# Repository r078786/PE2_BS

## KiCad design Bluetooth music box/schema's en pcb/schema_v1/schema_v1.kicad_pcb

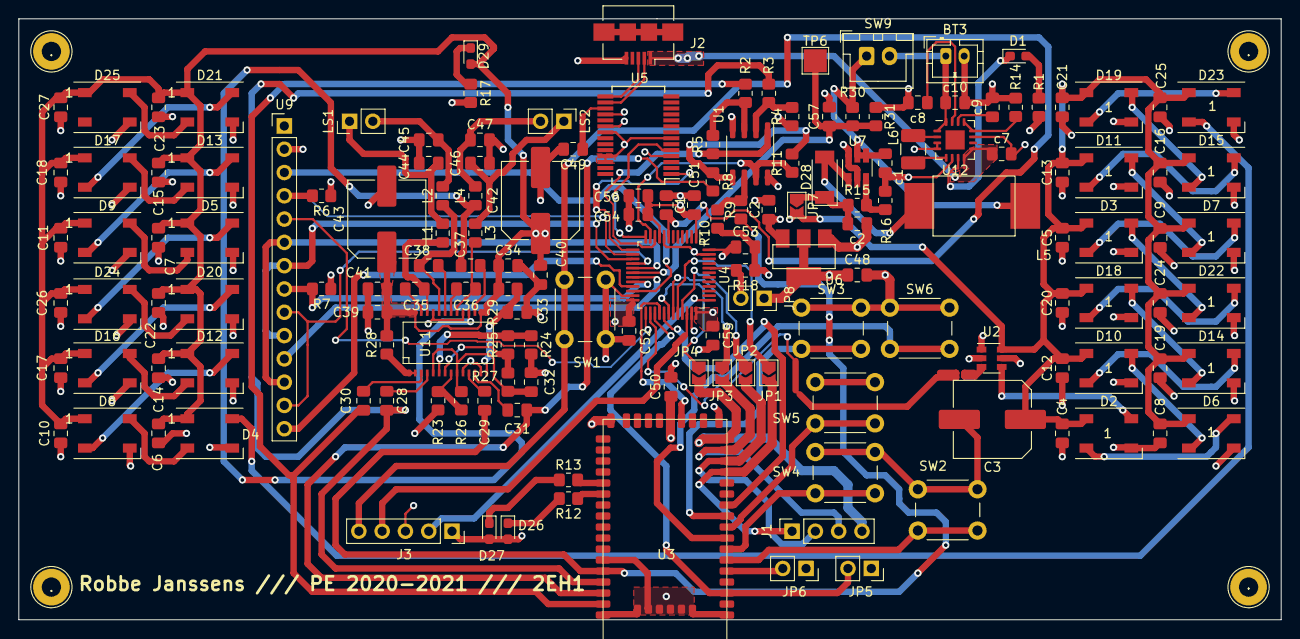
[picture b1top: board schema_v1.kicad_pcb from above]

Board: 4 copper layers, 137.7 x 65.5 mm, 161 parts (0 on the bottom side), 113 nets.

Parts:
., .#2, .#3, .#4: TestPoint_THTPad_D4.0mm_Drill2.0mm
BT3: Battery_Cell; JST_PH_B2B-PH-K_1x02_P2.00mm_Vertical
C1, C4, C5, C6, C7, C8, C9, C10, C11, C12, C13, C14, C15, C16, C17, C18, C19, C20, C21, C22, C23, C24, C25, C26, C27, C40, C41, C48, C49, C51, C52, C53, C54, C55, C57: 100nF; C_0805_2012Metric_Pad1.18x1.45mm_HandSolder
C2, C50: 10uF; C_0805_2012Metric_Pad1.18x1.45mm_HandSolder
C3, C42, C43: 100µF; C_Elec_8x10.2
C28, C29, C30, C31, C32, C33: 1µF; C_0805_2012Metric_Pad1.18x1.45mm_HandSolder
C34, C39: 1nF; C_0805_2012Metric_Pad1.18x1.45mm_HandSolder
C35, C36, C37, C38: 220nF; C_0805_2012Metric_Pad1.18x1.45mm_HandSolder
C44, C45, C46, C47: 2µ2F; C_0805_2012Metric_Pad1.18x1.45mm_HandSolder
C56: 10nF; C_0805_2012Metric_Pad1.18x1.45mm_HandSolder
D1: LED; LED_0603_1608Metric_Pad1.05x0.95mm_HandSolder
D2, D3, D4, D5, D6, D7, D8, D9, D10, D11, D12, D13, D14, D15, D16, D17, D18, D19, D20, D21, D22, D23, D24, D25: WS2812B; LED_WS2812B_PLCC4_5.0x5.0mm_P3.2mm
D26: BLUE; LED_0603_1608Metric_Pad1.05x0.95mm_HandSolder
D27, D29: RED; LED_0603_1608Metric_Pad1.05x0.95mm_HandSolder
D28: D_Schottky; D_SOD-128
J1: Conn_01x04; PinSocket_1x04_P2.54mm_Vertical
J2: USB_B_Micro; USB_Micro-B_Amphenol_10104110_Horizontal
J3: Conn_01x05_Male; PinSocket_1x05_P2.54mm_Vertical
JP1, JP2, JP3, JP4, JP7: SolderJumper; SolderJumper-2_P1.3mm_Open_TrianglePad1.0x1.5mm
JP5, JP6, JP8: Jumper; PinSocket_1x02_P2.54mm_Vertical
L1, L2, L3, L4: 15µH; L_0805_2012Metric_Pad1.15x1.40mm_HandSolder
L5: 2.2uH; L_tps563200
L6: 1.5µH; L_1210_3225Metric_Pad1.42x2.65mm_HandSolder
LS1, LS2: 8 Ohm; PinHeader_1x02_P2.54mm_Vertical
R1: 1k; R_0805_2012Metric_Pad1.20x1.40mm_HandSolder
R2, R3, R8, R9: 100K; R_0805_2012Metric_Pad1.20x1.40mm_HandSolder
R4, R5, R10, R11: 220K; R_0805_2012Metric_Pad1.20x1.40mm_HandSolder
R6, R7, R28: 10k; R_0805_2012Metric_Pad1.20x1.40mm_HandSolder
R12, R13, R17: 100; R_0805_2012Metric_Pad1.20x1.40mm_HandSolder
R14: 560; R_0805_2012Metric_Pad1.20x1.40mm_HandSolder
R15: 562K; R_0805_2012Metric_Pad1.20x1.40mm_HandSolder
R16: 107K; R_0805_2012Metric_Pad1.20x1.40mm_HandSolder
R18: 10K; R_0805_2012Metric_Pad1.20x1.40mm_HandSolder
R23: 39k; R_0805_2012Metric_Pad1.20x1.40mm_HandSolder
R24, R25, R27, R30: 33k; R_0805_2012Metric_Pad1.20x1.40mm_HandSolder
R26: 56k; R_0805_2012Metric_Pad1.20x1.40mm_HandSolder
R29: 10; R_0805_2012Metric_Pad1.20x1.40mm_HandSolder
R31: 100k; R_0805_2012Metric_Pad1.20x1.40mm_HandSolder
SW1, SW2, SW3, SW4, SW5, SW6: SW_Push; SW_PUSH_6mm_H7.3mm
SW9: Switch; JST_XH_B2B-XH-A_1x02_P2.50mm_Vertical
TP6: TestPoint; TestPoint_Pad_2.5x2.5mm
U1: TL072; SO-8_3.9x4.9mm_P1.27mm
U2: SN74LVC1T45DBV; SOT-23-6
U3: RN52
U4: STM32L443CCTx; LQFP-48_7x7mm_P0.5mm
U5: FT232RL; SSOP-28_5.3x10.2mm_P0.65mm
U6: LM1117-3.3; LM1117
U7: TLV61048; SOT-23-6_Handsoldering
U9: Spi_header; PinHeader_1x14_P2.54mm_Vertical
U11: tpa3140
U12: LTC4001; QFN-16-1EP_4x4mm_P0.65mm_EP2.1x2.1mm
c1: 1uF; C_0805_2012Metric_Pad1.18x1.45mm_HandSolder
c2, c7, c10: 10µF; C_0805_2012Metric_Pad1.18x1.45mm_HandSolder
c8: 0.22µF; C_0805_2012Metric_Pad1.18x1.45mm_HandSolder
c9: 0.1µF; C_0805_2012Metric_Pad1.18x1.45mm_HandSolder

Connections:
+3V3: C48.1, C50.1, C51.1, C52.1, C53.1, C54.1, C55.1, C56.1, D26.2, D27.2, J3.1, JP5.1, JP6.1, JP8.1, R1.1, R6.1, R7.1, U1.8, U2.1, U2.5, U3.22, U4.1, U4.9, U4.24, U4.36, U4.48, U5.4, U5.20, U6.2, U9.1
+5V: C2.1, C3.1, C4.1, C5.1, C6.1, C7.1, C8.1, C9.1, C10.1, C11.1, C12.1, C13.1, C14.1, C15.1, C16.1, C17.1, C18.1, C19.1, C20.1, C21.1, C22.1, C23.1, C24.1, C25.1, C26.1, C27.1, C34.1, C39.1, C40.1, C41.1, C42.1, C43.1, D2.1, D3.1, D4.1, D5.1, D6.1, D7.1, D8.1, D9.1, D10.1, D11.1, D12.1, D13.1, D14.1, D15.1, D16.1, D17.1, D18.1, D19.1, D20.1, D21.1, D22.1, D23.1, D24.1, D25.1, D29.2, JP7.2, R28.2, R29.1, U2.6, U6.3, U11.15, U11.16, U11.27, U11.28
/BT_Audio/FACT_RESET: JP6.2, U3.5
/L+: C30.2, R2.2, U3.43
/L-: C28.2, R3.2, U3.41
/LEDS/FirstLED: D2.4, U2.4
/L_SE: R5.1, U1.1, U4.10
/R+: C31.2, R8.2, U3.42
/R-: C29.2, R9.2, U3.40
/R_SE: R11.1, U1.7, U4.11
/STM32G0/SWDCLK: J3.2, U4.37
/STM32G0/SWDIO: J3.4, U4.34
BAT_ADC: C57.1, R30.2, R31.1, TP6.1, U4.18
CTS_BT: JP2.1, U4.33
EVENT: JP5.2, U3.3, U4.27
GND: BT3.2, C1.1, C2.2, C3.2, C4.2, C5.2, C6.2, C7.2, C8.2, C9.2, C10.2, C11.2, C12.2, C13.2, C14.2, C15.2, C16.2, C17.2, C18.2, C19.2, C20.2, C21.2, C22.2, C23.2, C24.2, C25.2, C26.2, C27.2, C32.2, C33.2, C34.2, C39.2, C40.2, C41.2, C42.2, C43.2, C44.1, C45.2, C46.1, C47.2, C48.2, C49.2, C50.2, C51.2, C52.2, C53.2, C54.2, C55.2, C56.2, C57.2, D2.3, D3.3, D4.3, D5.3, D6.3, D7.3, D8.3, D9.3, D10.3, D11.3, D12.3, D13.3, D14.3, D15.3, D16.3, D17.3, D18.3, D19.3, D20.3, D21.3, D22.3, D23.3, D24.3, D25.3, J2.5, J3.3, R4.1, R10.1, R14.1, R16.2, R17.2, R18.1, R23.2, R24.2, R31.2, SW1.1, SW2.1, SW3.1, SW4.1, SW5.1, SW6.1, U1.4, U2.2, U3.1, U3.18, U3.27, U3.39, U3.44, U3.45, U3.46, U3.47, U3.48, U3.49, U3.50, U4.8, U4.23, U4.35, U4.47, U5.7, U5.18, U5.21, U5.25, U5.26, U6.1, U7.2, U7.6, U9.2, U11.10, U11.13, U11.19, U11.24, U12.3, U12.4, U12.6, U12.11, c1.2, c2.2, c7.2, c8.2, c9.2, c10.2
LCD_CS: U4.22, U9.3
LCD_DC: U4.25, U9.5
LCD_LED: R7.2, U4.20, U9.8
LCD_SCK: U4.15, U9.7, U9.10
LCD_SDI: U4.17, U9.6, U9.12
LCD_SDO: U4.16, U9.9, U9.13
LCD_T_CS: U4.19, U9.11
LCD_T_Irq: U4.21, U9.14
LCD_rst: R6.2, U4.14, U9.4
MODE: U3.11, U4.29
unnamed: BT3.1, SW9.2, U12.1, U12.16, c10.1
unnamed: C28.1, U11.4
unnamed: C29.1, U11.11
unnamed: C30.1, U11.3
unnamed: C31.1, U11.12
unnamed: C32.1, R26.1, R27.1, U11.5, U11.9
unnamed: C33.1, R29.2, U11.14
unnamed: C35.1, U11.22
unnamed: C35.2, L2.1, U11.23
unnamed: C36.1, U11.21
unnamed: C36.2, L3.1, U11.20
unnamed: C37.1, U11.17
unnamed: C37.2, L4.1, U11.18
unnamed: C38.1, U11.26
unnamed: C38.2, L1.1, U11.25
unnamed: C44.2, L1.2, LS1.1
unnamed: C45.1, L2.2, LS1.2
unnamed: C46.2, L3.2, LS2.1
unnamed: C47.1, L4.2, LS2.2
unnamed: C49.1, U5.17
unnamed: D1.1, U12.7
unnamed: D1.2, R1.2
unnamed: D2.2, D6.4
unnamed: D3.2, D7.4
unnamed: D4.2, D8.4
unnamed: D5.2, D9.4
unnamed: D10.2, D14.4
unnamed: D6.2, D10.4
unnamed: D11.2, D15.4
unnamed: D7.2, D11.4
unnamed: D12.2, D16.4
unnamed: D8.2, D12.4
unnamed: D13.2, D17.4
unnamed: D9.2, D13.4
unnamed: D14.2, D18.4
unnamed: D15.2, D19.4
unnamed: D16.2, D20.4
unnamed: D17.2, D21.4
unnamed: D18.2, D22.4
unnamed: D19.2, D23.4
unnamed: D20.2, D24.4
unnamed: D21.2, D25.4
unnamed: D3.4, D22.2
unnamed: D4.4, D23.2
unnamed: D5.4, D24.2
unnamed: D26.1, R12.2
unnamed: D27.1, R13.2
unnamed: D28.1, JP7.1, R15.1, c2.1
unnamed: D28.2, L5.2, U7.1
unnamed: D29.1, R17.1
unnamed: J1.1, JP1.2, U3.14
unnamed: J1.2, JP2.2, U3.15
unnamed: J1.3, JP3.2, U3.16
unnamed: J1.4, JP4.2, U3.17
unnamed: J2.2, U5.16
unnamed: J2.3, U5.15
unnamed: JP8.2, R18.2, U4.44
unnamed: L6.1, U12.5
unnamed: L6.2, U12.2
unnamed: R2.1, R5.2, U1.3
unnamed: R3.1, R4.2, U1.2
unnamed: R9.1, R10.2, U1.6
unnamed: R8.1, R11.2, U1.5
unnamed: R12.1, U3.33
unnamed: R13.1, U3.32
unnamed: R14.2, U12.12, U12.13
unnamed: R15.2, R16.1, U7.3
unnamed: R23.1, R26.2, U11.8
unnamed: R24.1, R25.2, U11.6
unnamed: R25.1, R27.2, U11.7
unnamed: R28.1, U11.1, U11.2
unnamed: U12.14, c9.1
unnamed: U12.15, c8.1
RTS_BT: JP1.1, U4.32
RX: U4.13, U5.1
RX_BT: JP4.1, U4.30
Reset: C1.2, J3.5, SW1.2, U4.7
TX: U4.12, U5.5
TX_BT: JP3.1, U4.31
Vbat: L5.1, R30.1, SW9.1, U7.4, U7.5, c1.1
Vusb: J2.1, U12.8, U12.9, c7.1
WAKE: U3.21, U4.28
next: SW4.2, U3.7
pp: SW6.2, U3.8
prev: SW5.2, U3.9
vol+: SW2.2, U3.6
vol-: SW3.2, U3.10

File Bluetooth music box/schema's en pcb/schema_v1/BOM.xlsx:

Ref | Qnty | Value | Part | Datasheet | Description | Vendor
10uF10, 10uF11 | 2 | 22µF | Device:C | ~ | Unpolarized capacitor | https://www.mouser.be/ProductDetail/Taiyo-Yuden/TMK325B7226M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
BT3 | 1 | Battery_Cell | Device:Battery_Cell | ~ | Single-cell battery
C3, C42, C43 | 3 | 100µF | Device:CP1 | ~ | Polarized capacitor, US symbol | https://www.mouser.be/ProductDetail/Panasonic/EEH-ZF1V101P?q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
C4, C5, C6, C7, C8, C9, C10, C11, C12, C13, C14, C15, C16, C17, C18, C19, C20, 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 | 31 | 100nF | Device:C | ~ | Unpolarized capacitor | https://www.mouser.be/ProductDetail/Taiyo-Yuden/HMF325B7104K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
c7, c10, 10uF1, 10uF7, 10uF8 | 5 | 10µF | Device:C | ~ | Unpolarized capacitor | https://www.mouser.be/ProductDetail/Taiyo-Yuden/LMF325B7106K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
c8 | 1 | 0.22µF | Device:C | ~ | Unpolarized capacitor | https://www.mouser.be/ProductDetail/Taiyo-Yuden/HMF325B7224K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
c9, 10uF9 | 2 | 0.1µF | Device:C | ~ | Unpolarized capacitor | https://www.mouser.be/ProductDetail/Taiyo-Yuden/HMF325B7104K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
C28, C29, C30, C31, C32, C33 | 6 | 1µF | Device:C | ~ | Unpolarized capacitor | https://www.mouser.be/ProductDetail/Taiyo-Yuden/UMK325LD105K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
C34, C39 | 2 | 1nF | Device:C | ~ | Unpolarized capacitor | https://www.mouser.be/ProductDetail/Taiyo-Yuden/HMF316B7102K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
C35, C36, C37, C38 | 4 | 220nF | Device:C | ~ | Unpolarized capacitor | https://www.mouser.be/ProductDetail/Taiyo-Yuden/HMF325B7224K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
C44, C45, C46, C47 | 4 | 2µ2F | Device:C | ~ | Unpolarized capacitor | https://www.mouser.be/ProductDetail/Taiyo-Yuden/HMF325B7225M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
D1 | 1 | LED | Device:LED | ~ | Light emitting diode | Heb ik zelf
D2, D3, D4, D5, D6, D7, D8, D9, D10, D11, D12, D13, D14, D15, D16, D17, D18, D1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 | 24 | WS2812B | LED:WS2812B | https://cdn-shop.adafruit.com/datasheets/WS2812B.pdf | RGB LED with integrated controller | aan stijn vragen (in orde)
J1 | 1 | Pickit aansluiting | Connector:Conn_01x05_Male | ~ | Generic connector, single row, 01x05, script generated (kicad-library-utils/sch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 | https://www.mouser.be/ProductDetail/Harwin/M50-3930542?qs=%2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
J2 | 1 | USB_B_Micro | Connector:USB_B_Micro | ~ | USB Micro Type B connector | https://www.mouser.be/ProductDetail/Wurth-Elektronik/6291051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
JP1 | 1 | SolderJumper | schema_v1-rescue:Jumper_SolderJumper_2_Open-Bluetooth_Speaker-cache |  |  | /
L1, L2, L3, L4 | 4 | 15µH | Device:L | ~ | Inductor | https://www.mouser.be/ProductDetail/Murata-Electronics/LQM21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
L6 | 1 | 1.5µH | Device:L | ~ | Inductor | https://www.mouser.be/ProductDetail/TDK/TFM322512ALMA1R5MTAA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
L8 | 1 | 2.2uH | Device:L | ~ | Inductor | https://www.mouser.be/ProductDetail/TDK/SPM10065VT-2R2M-D?qs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
LS1, LS2 | 2 | 8 Ohm | Device:Speaker | ~ | Speaker | heb ik zelf
R1, R3, R4, R6, R7, R10, R11, R13, R16, R20, R22, R28, R32, R37 | 14 | 10k | Device:R | ~ | Resistor | https://www.mouser.be/ProductDetail/Panasonic/ERA-6VEB1002V?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
R2 | 1 | 100 | Device:R | ~ | Resistor | https://www.mouser.be/ProductDetail/Panasonic/ERA-6VEB1000V?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
R14 | 1 | 560 | Device:R | ~ | Resistor | https://www.mouser.be/ProductDetail/Panasonic/ERA-6APB561V?q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
R23 | 1 | 39k | Device:R | ~ | Resistor | https://www.mouser.be/ProductDetail/Panasonic/ERA-6ARW393V?q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
R24, R25, R27, R30 | 4 | 33k | Device:R | ~ | Resistor | https://www.mouser.be/ProductDetail/Panasonic/ERA-6ARW333V?q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
R26, R36 | 2 | 56k | Device:R | ~ | Resistor | https://www.mouser.be/ProductDetail/Panasonic/ERA-6ARW563V?q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
R29 | 1 | 10 | Device:R | ~ | Resistor | https://www.mouser.be/ProductDetail/Panasonic/ERJ-U06J100V?q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
D26 | 1 | 1,8V | Zener Diode | ~ | zener diode | https://www.mouser.be/ProductDetail/Comchip-Technology/MMSZ4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
R5, R8, R9, R31 | 4 | 100k | Device:R | ~ | Resistor | https://www.mouser.be/ProductDetail/Panasonic/ERA-6VEB1003V?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
SW1, SW3, SW4, SW5, SW6, SW7 | 6 | SW_Push | Switch:SW_Push | ~ | Push button switch, generic, two pins | https://www.mouser.be/ProductDetail/CK/PTS645SK43JSMTR92-LFS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
SW9 | 1 | Switch | schema_v1-rescue:Switch-Robbe_TI |  |  | https://www.mouser.be/ProductDetail/Bulgin/C1353ATNAN?qs=T3o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
U1 | 1 | LTC2063 | Robbe_random:LTC2064 |  |  | https://www.mouser.be/ProductDetail/Analog-Devices/LTC2063IS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
U2 | 1 | pic18f27k40 | schema_v1-rescue:pic18f27k40-Robbe_TI |  |  | heb ik zelf
U5 | 1 | FT232RL | Interface_USB:FT232RL | https://www.ftdichip.com/Support/Documents/DataSheets/ICs/DS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 | USB to Serial Interface, SSOP-28 | https://www.mouser.be/ProductDetail/FTDI/FT232RL-REEL?qs=D1%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
U6 | 1 | LM1117-3.3 | Regulator_Linear:LM1117-3.3 | http://www.ti.com/lit/ds/symlink/lm1117.pdf | 800mA Low-Dropout Linear Regulator, 3.3V fixed output, TO-220/TO-252/TO-263/SOT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 | https://www.mouser.be/ProductDetail/Texas-Instruments/LM1117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
U8 | 1 | OVC3860_EDR | schema_v1-rescue:OVC3860_EDR-Robbe_random |  |  | al besteld
U9 | 1 | Spi_header | schema_v1-rescue:Spi_header-Robbe_random |  |  | https://www.mouser.be/ProductDetail/Harwin/M20-7821446?qs=Jp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
U10 | 1 | SN74LVC1T45DBV | Logic_LevelTranslator:SN74LVC1T45DBV | http://www.ti.com/lit/ds/symlink/sn74lvc1t45.pdf | Single-Bit Dual-Supply Bus Transceiver With Configurable Voltage Translation an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 | https://www.mouser.be/ProductDetail/Texas-Instruments/SN74LV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
U11 | 1 | tpa3140 | schema_v1-rescue:tpa3140-Robbe_random |  |  | https://www.mouser.be/ProductDetail/Texas-Instruments/TPA314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
U12 | 1 | LTC4001 | Robbe_random:LTC4001 |  |  | https://www.mouser.be/ProductDetail/Analog-Devices/LTC4001EU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
U14 | 1 | TPS563200 | Regulator_Switching:TPS563200 | http://www.ti.com/lit/ds/symlink/tps563200.pdf | 3A Synchronous Step-Down Voltage Regulator, Adjustable Output Voltage, 4.5-17V 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 | https://sinuss.be/componenten/halfgeleiders-sensors/ics/volt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
Bestelling
sinuss | 10.49 |  | besteld
pcb | 56.85 |  | besteld
mouser | 139.82 |  | besteld
aliexpress | 11.3 |  | besteld
totaal | 218.46

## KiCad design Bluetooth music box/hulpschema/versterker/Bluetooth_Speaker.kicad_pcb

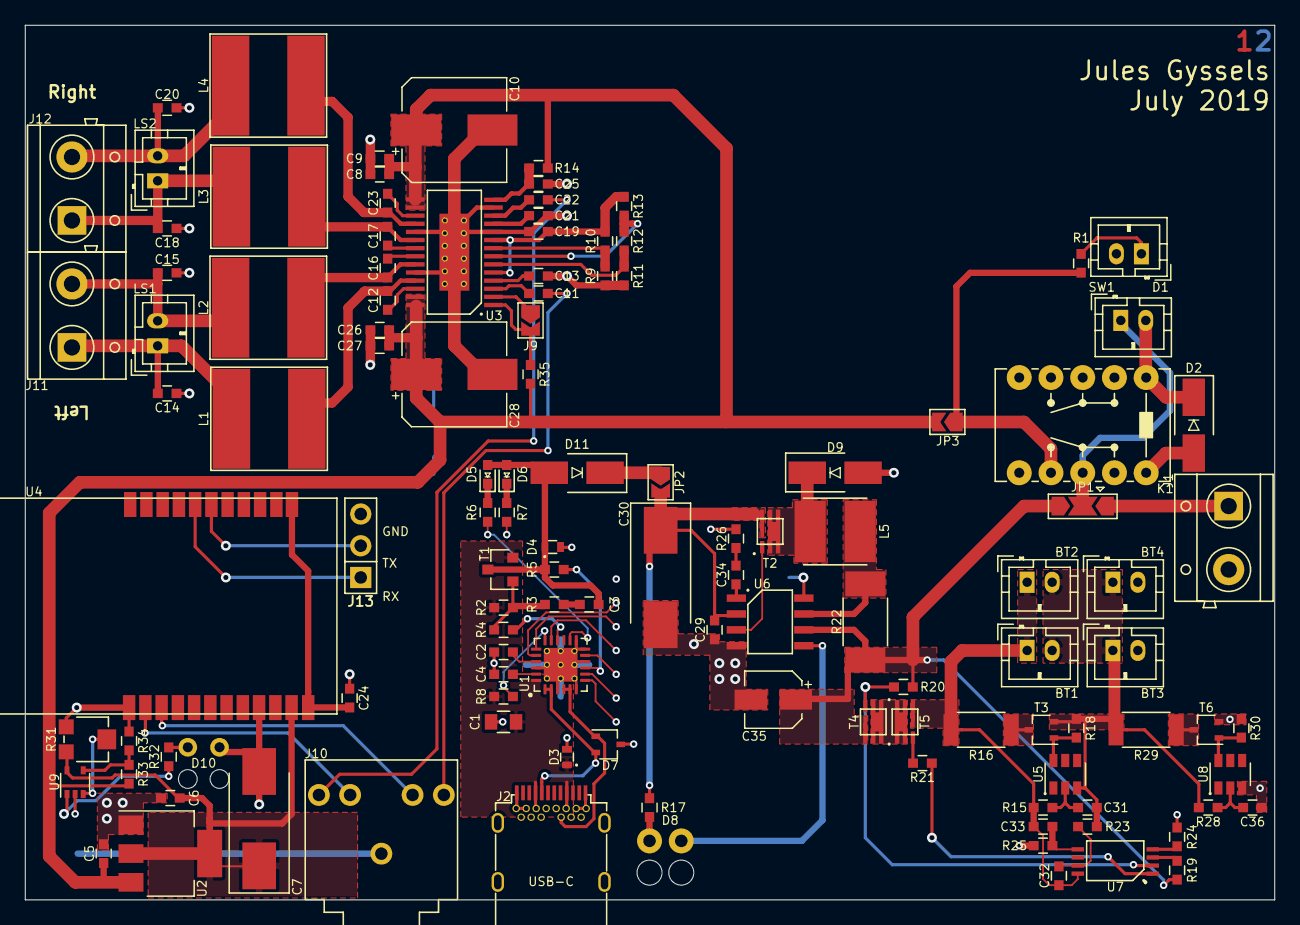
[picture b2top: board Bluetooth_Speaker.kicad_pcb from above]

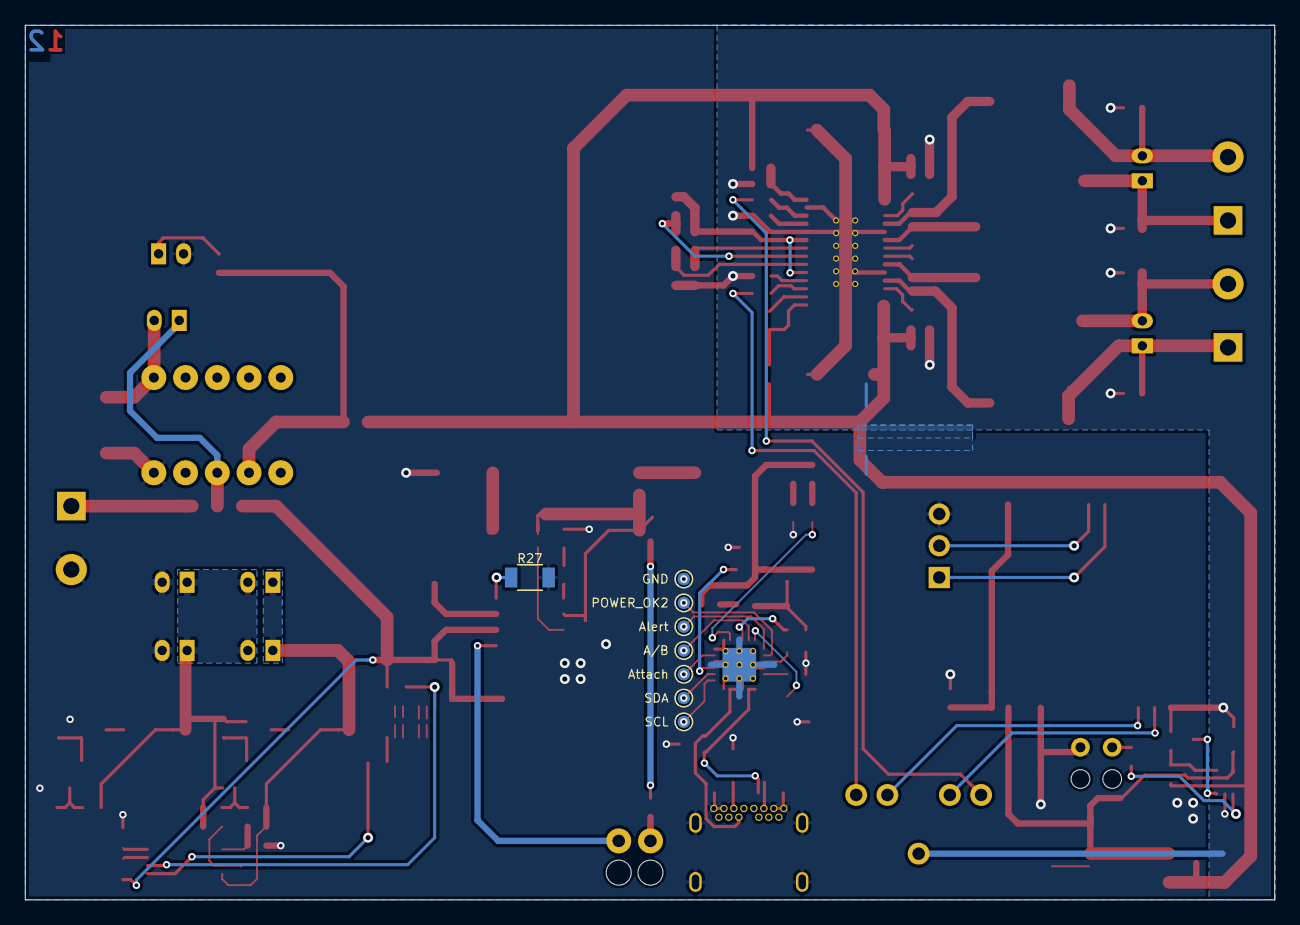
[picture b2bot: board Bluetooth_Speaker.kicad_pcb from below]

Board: 2 copper layers, 100.0 x 70.0 mm, 127 parts (8 on the bottom side), 90 nets.

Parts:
BT1, BT2, BT3, BT4: BatteryCell; JST_PH_B2B-PH-K_02x2.00mm_Straight
C1: 4.7u; C_0805
C2, C4, C11, C13, C14, C15, C18, C19, C20, C21, C22, C25: 1uF; C_0603
C3, C5, C6, C9, C24, C27, C29, C31, C32, C36: 100nF; C_0603
C7, C30: 10uF; CP_Tantalum_Case-D_EIA-7343-31_HandSoldering
C8, C26: 1nF; C_0603
C10, C28: 100uF; CP_Elec_8x10.5
C12, C16, C17, C23: 220nF; C_0603
C33: 2.2uF; C_0603
C34: 0.47uF; C_0603
C35: 22uF; CP_Elec_4x5.7
D1: LED; JST_PH_B2B-PH-K_02x2.00mm_Straight
D2: Diode; D_SMA
D3, D4: ESDA25P35; QFN1610
D5, D6: LED; L_0603
D7: ESDA25W; SOT-323_SC-70
D8, D10: LED; _Jules_WireStressRelief_x2
D9: B330; D_SMA
D11: 1N4001; D_SMA
J1: V_IN; TerminalBlock_02x5.08mm
J2: USB-C; USB-C_Wurth_632723x00011
J3: Power_OK2; TestPoint_Pad_D1.0mm
J4: A_B_Side; TestPoint_Pad_D1.0mm
J5: Attach; TestPoint_Pad_D1.0mm
J6: SCL; TestPoint_Pad_D1.0mm
J7: SDA; TestPoint_Pad_D1.0mm
J8: Alert; TestPoint_Pad_D1.0mm
J9: AutoRecovery; SolderJumper-2_P1.3mm_Open_TrianglePad1.0x1.5mm
J10: Audio-Jack-5_Switched; Audio_Jack-5
J11: OUT_L; TerminalBlock_02x5.08mm
J12: OUT_R; TerminalBlock_02x5.08mm
J13: UART; Pin_Header_Straight_1x03_Pitch2.54mm
J14: GND; TestPoint_Pad_D1.0mm
JP1: SolderJumper_3_Open; SolderJumper-3_P2.0mm_Open_TrianglePad1.0x1.5mm
JP2, JP3: SolderJumper_2_Open; SolderJumper-2_P1.3mm_Open_TrianglePad1.0x1.5mm
K1: DPDT_Relays; TQ2SA-L-9V
L1, L2, L3, L4: 33uH; Laird_TYS8040330M
L5: 15uH; Murata_LQH5BPN150M38L
LS1, LS2: 4-8 Ohm; JST_PH_B2B-PH-K_02x2.00mm_Straight
R1, R6, R7, R17: 3k9; R_0603
R2: 100k; R_0603
R3, R15, R28, R32: 100; R_0603
R4, R33: 22k; R_0603
R5, R8, R20, R23, R24: 1k; R_0603
R9: 39k; R_0603
R10: 56k; R_0603
R11, R12, R13: 33k; R_0603
R14: 10; R_0603
R16, R29: 51; R_2010
R18, R30, R35: 10k; R_0603
R19, R21: 5.1k; R_0603
R22: 75m; R_2512
R25: 51; R_0603
R26: 2k2; R_0603
R27: 10K; R_1206
R31: 100k; Trimmer_3mm
R34: 12k; R_0603
SW1: SPST_NO; JST_PH_B2B-PH-K_02x2.00mm_Straight
T1: SI2369DS; SOT-23
T2, T4, T5: SIA471DJ; SC-70-6L
T3, T6: BSS816NW; SOT-323_SC-70
U1: STUSB4500; QFN-24-1EP_4x4mm_P0.5mm_EP2.7x2.7mm_ThermalVias
U2: LM1117-3.3; SOT-223-3Lead_TabPin2
U3: TPA3140; HTSSOP-28-_4.4x9.7mm_Pitch0.65_EP6.17x2.4mm
U4: OVC3860
U5, U8: HY2213; SOT-23-6
U6: LTC4002; SOIC-8_3.9x4.9mm_Pitch1.27mm
U7: S-8253A; TSSOP-8_4.4x3mm_Pitch0.65mm
U9: NCX2200GW; SOT-353_SC-70-5

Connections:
+3V3: C6.2, C7.1, R31.2, U2.2, U4.29, U9.5
/Audio_Amplifier/Bluetooth_L: J10.5, U4.19
/Audio_Amplifier/Bluetooth_R: J10.3, U4.17
/Battery_Charge_Circuit/V_Batt: C35.1, JP1.3, R19.2, R20.2, R22.1, T4.2, U6.6
/Battery_Charge_Circuit/V_USB: C29.2, C30.1, JP2.2, R17.2, T2.2, U6.2
/USB-C_Charger/Vbus: C1.2, D3.1, J2.A4, J2.A9, J2.B4, J2.B9, R2.1, R8.1, T1.2, U1.24
Audio_L: C11.1, J10.2
Audio_R: C22.1, J10.4
CC1: D7.2, J2.A5, U1.1, U1.2
CC2: D7.1, J2.B5, U1.4, U1.5
GNDA: C8.1, C9.1, C10.2, C13.1, C14.2, C15.1, C18.2, C19.2, C20.1, C21.1, C25.1, C26.1, C27.1, C28.2, J10.1, R9.1, R11.1, R31.1, R34.1, U3.10, U3.13, U3.19, U3.24, U3.29, U4.16, U9.2
GNDD: BT3.2, BT4.2, C1.1, C2.1, C4.1, C5.1, C6.1, C7.2, C24.1, C29.1, C30.2, C35.2, C36.1, D1.2, D2.1, D3.2, D4.2, D7.3, D9.1, D10.2, J1.2, J2.A1, J2.A12, J2.B1, J2.B12, J2.SH, J13.3, J14.1, K1.1, R7.1, R24.2, R25.2, R26.1, R27.2, R30.1, T6.2, U1.3, U1.6, U1.10, U1.12, U1.13, U1.22, U1.25, U2.1, U4.31, U6.4, U8.3
unnamed: BT1.1, BT2.1, C32.2, C33.2, R15.2, R16.2, T5.2, U7.8
unnamed: BT1.2, BT2.2, BT3.1, BT4.1, C31.1, R18.1, R23.2, R28.2, R29.2, T3.2, U5.3
unnamed: C2.2, U1.21
unnamed: C3.1, R3.2
unnamed: C4.2, U1.23
unnamed: C11.2, U3.3
unnamed: C12.1, U3.26
unnamed: C12.2, L1.1, U3.25
unnamed: C13.2, U3.4
unnamed: C14.1, J11.1, L1.2, LS1.1
unnamed: C15.2, J11.2, L2.1, LS1.2
unnamed: C16.1, U3.22
unnamed: C16.2, L2.2, U3.23
unnamed: C17.1, U3.21
unnamed: C17.2, L3.1, U3.20
unnamed: C18.1, J12.1, L3.2, LS2.1
unnamed: C19.1, R10.2, R13.2, U3.5, U3.9
unnamed: C20.2, J12.2, L4.1, LS2.2
unnamed: C21.2, U3.11
unnamed: C22.2, U3.12
unnamed: C23.1, U3.17
unnamed: C23.2, L4.2, U3.18
unnamed: C24.2, U4.33, U4.35
unnamed: C25.2, R14.1, U3.14
unnamed: C31.2, R15.1, U5.2
unnamed: C32.1, R23.1, U7.7
unnamed: C33.1, R25.1, U7.5
unnamed: C34.1, R26.2
unnamed: C34.2, U6.1
unnamed: C36.2, R28.1, U8.2
unnamed: D1.1, R1.1
unnamed: D2.2, K1.10, SW1.2
unnamed: D5.2, R6.2
unnamed: D6.2, R7.2
unnamed: D8.1, R17.1
unnamed: D8.2, U6.5
unnamed: D9.2, L5.1, T2.3
unnamed: D10.1, R32.2
unnamed: D11.2, JP2.1
unnamed: J1.1, JP1.1
unnamed: J3.1, U1.20
unnamed: J4.1, U1.17
unnamed: J5.1, U1.11
unnamed: J6.1, U1.7
unnamed: J7.1, U1.8
unnamed: J8.1, U1.19
unnamed: J9.1, U3.2
unnamed: J9.2, R35.2, U3.1
unnamed: J13.1, U4.44
unnamed: J13.2, U4.43
unnamed: JP1.2, K1.3, SW1.1
unnamed: JP3.1, K1.4, R1.2
unnamed: L5.2, R22.2, U6.7
unnamed: R2.2, R3.1, R4.2, T1.1
unnamed: R4.1, U1.16
unnamed: R5.1, U1.9
unnamed: R6.1, U1.14
unnamed: R8.2, U1.18
unnamed: R9.2, R10.1, U3.8
unnamed: R11.2, R12.1, U3.6
unnamed: R12.2, R13.1, U3.7
unnamed: R16.1, T3.3
unnamed: R18.2, T3.1, U5.6
unnamed: R19.1, U7.3
unnamed: R20.1, T4.1, U7.2
unnamed: R21.1, U7.1
unnamed: R21.2, T5.1
unnamed: R24.1, U7.4
unnamed: R27.1, U6.8
unnamed: R29.1, T6.3
unnamed: R30.2, T6.1, U8.6
unnamed: R31.3, U9.3
unnamed: R32.1, U9.1
unnamed: R33.2, R34.2, U9.4
unnamed: T2.1, U6.3
unnamed: T4.3, T5.3
VDD: C5.2, C8.2, C9.2, C10.1, C26.2, C27.2, C28.1, JP3.2, R14.2, R33.1, R35.1, U2.3, U3.15, U3.16, U3.27, U3.28
Vsink: C3.2, D4.1, D5.1, D6.1, D11.1, R5.2, T1.3

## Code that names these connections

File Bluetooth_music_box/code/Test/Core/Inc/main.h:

/* USER CODE BEGIN Header */
/**
  ******************************************************************************
  * @file           : main.h
  * @brief          : Header for main.c file.
  *                   This file contains the common defines of the application.
  ******************************************************************************
  * @attention
  *
  * <h2><center>&copy; Copyright (c) 2021 STMicroelectronics.
  * All rights reserved.</center></h2>
  *
  * This software component is licensed by ST under BSD 3-Clause license,
  * the "License"; You may not use this file except in compliance with the
  * License. You may obtain a copy of the License at:
  *                        opensource.org/licenses/BSD-3-Clause
  *
  ******************************************************************************
  */
/* USER CODE END Header */

/* Define to prevent recursive inclusion -------------------------------------*/
#ifndef __MAIN_H
#define __MAIN_H

#ifdef __cplusplus
extern "C" {
#endif

/* Includes ------------------------------------------------------------------*/
#include "stm32l4xx_hal.h"

/* Private includes ----------------------------------------------------------*/
/* USER CODE BEGIN Includes */

/* USER CODE END Includes */

/* Exported types ------------------------------------------------------------*/
/* USER CODE BEGIN ET */

/* USER CODE END ET */

/* Exported constants --------------------------------------------------------*/
/* USER CODE BEGIN EC */

/* USER CODE END EC */

/* Exported macro ------------------------------------------------------------*/
/* USER CODE BEGIN EM */

/* USER CODE END EM */

/* Exported functions prototypes ---------------------------------------------*/
void Error_Handler(void);

/* USER CODE BEGIN EFP */

/* USER CODE END EFP */

/* Private defines -----------------------------------------------------------*/
#define IN_LEFT_Pin GPIO_PIN_0
#define IN_LEFT_GPIO_Port GPIOA
#define IN_RIGHT_Pin GPIO_PIN_1
#define IN_RIGHT_GPIO_Port GPIOA
#define LCD_RST_Pin GPIO_PIN_4
#define LCD_RST_GPIO_Port GPIOA
#define BATTERY_Pin GPIO_PIN_0
#define BATTERY_GPIO_Port GPIOB
#define TOUCH_CS_Pin GPIO_PIN_1
#define TOUCH_CS_GPIO_Port GPIOB
#define BACKLIGHT_Pin GPIO_PIN_2
#define BACKLIGHT_GPIO_Port GPIOB
#define TOUCH_IRQ_Pin GPIO_PIN_10
#define TOUCH_IRQ_GPIO_Port GPIOB
#define LCD_CS_Pin GPIO_PIN_11
#define LCD_CS_GPIO_Port GPIOB
#define LCD_DC_Pin GPIO_PIN_12
#define LCD_DC_GPIO_Port GPIOB
#define EVENT_Pin GPIO_PIN_14
#define EVENT_GPIO_Port GPIOB
#define WAKE_Pin GPIO_PIN_15
#define WAKE_GPIO_Port GPIOB
#define MODE_Pin GPIO_PIN_8
#define MODE_GPIO_Port GPIOA
/* USER CODE BEGIN Private defines */

/* USER CODE END Private defines */

#ifdef __cplusplus
}
#endif

#endif /* __MAIN_H */

/************************ (C) COPYRIGHT STMicroelectronics *****END OF FILE****/

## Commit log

2021-03-08 BlueTooth Speaker
2021-03-08 test change
2021-03-08 Update BOM.xlsx
    Added some order links
2021-03-08 aanpassing schema en pcb
    oplossing voor audiosignalen
    in excel nog enkele links toegevoegd
2021-03-09 aanpassingen bom, gerber files voor bestelling
2021-03-16 eerste code test
    nog niet getest, enkel geschreven
2021-03-17 Nieuwe start
    Nieuw schema (andere µC, BT-module, dc/dc, verschillversterkers)
2021-03-17 Werken aan positionering componenten op pcb
    kleine aanpassingen op schema (zoals verbinding leds - µc)
2021-03-18 pcb componenten goed gepositioneerd (pcb_v3)
2021-03-18 Tracks tekenen op pcb
2021-03-19 nieuwe pdf gemaakt om schema te laten nakijken
2021-03-19 pcb af
    laatste tracks verbonden
2021-03-21 pcb af en gerbers aangemaakt om te bestellen
2021-03-23 New repository
    New repository zodat ik kon werken in eclipse
2021-03-23 Final gerbers en eerste keer beginnen aan code
2021-03-24 Poging voor ili9341 driver
    Mislukt
2021-03-24 Poging 2 tot codering
    Mislukt
2021-03-30 Aanpassing code bestanden
    errors fixed
2021-03-30 Eerste testcode voor lcd
    Namen van functies van library veranderd
    op het scherm: kleuren weergeven, figuren, test met touch
    NOG NIET GETEST (pcb nog niet aangekomen)
2021-04-07 Clean UP
2021-04-07 Niet echt iets gedaan
    Na "clean up" gewoon nog eens getest
    Niks veranderd in code
2021-04-09 Poging tot LCD aan te praat te krijgen
    Niet gelukt, scherm ligt enkel op tijdens start en einde van de console in stm workbench
2021-04-10 scherm weergave deels gelukt
    tekst, kleuren en posities werken
    werkt niet: touch
2021-04-12 poging tot leds aan te sturen
    library + heel klein stukje testcode
    nog niet getest
2021-04-12 geprobeerd om iets te vinden over ws2812 leds
    niks gevonden..
2021-04-18 Touch geregeld, leds nog niet
    touch: 2 pins omgewisseld in de defines, snelheid spi veranderd
2021-04-20 poging tot images op lcd
    De afbeeldingen komen wel op het scherm, maar 90 graden gedraaid. Nog niet opgelost.
2021-04-20 Werken aan hoofdmenu
    indeling gemaakt voor naam v/h liedje, muziek luider/zachter, batterij, next, pause, previous
2021-04-20 poging tot slider van batterij
    niet gelukt
2021-04-25 start van document gemaakt "verslag.docx"
2021-04-26 enkel "mode-pin" aangestuurd voor poging tot BT module
    nog niet getest
2021-04-27 Library en uitvoering LEDS
    Werkt !
    adc ingang lezen en aansturen op leds nog niet....
2021-04-27 poging tot adc
    niet gelukt
2021-04-28 Gestart aan eindeverslag
    Structuur gegeven aan het verslag + heel de intro + kleine start van verslag zelf
2021-04-28 Aan verslag gewerkt
    Componenten toegevoegd, schematic deels uitgelegd
2021-05-02 prutsen met touch voor leds aan te sturen
    niet gelukt
2021-05-02 ADC audio werkt deels
    constante waarde op scherm
2021-05-02 hardware en behuizing aan verslag toegevoegd
    foto's geupload met een beetje tekst
2021-05-03 geprobeerd om adc werkend te krijgen + hoofdscherm aangepast
    niet gelukt.
    hoofdscherm andere layout
    toggle lcd_led functie
2021-05-04 Kan communiceren met BT via uart
    +LEDS13-24 werken niet meer
2021-05-09 klein beetje extra commentaar in code + toevoeging WS2812 in verslag
    Enkele dingen toegevoegd in het verslag
    grootste punt: Software; WS2812 aansturing helemaal uitgelegd
2021-05-11 Niet echt iets gedaan
    begin aan kleureffecten
    geprobeerd voor BT com
2021-05-13 behuizing getekend
2021-05-13 Clean gemaakt + led effect + power check
    code proper gemaakt:
    functies gemaakt, nutteloze code weggedaan
    led effect: regenboog
    power check: LCD / LEDs aan/uit
2021-05-14 Besluit getypt
2021-05-17 behuizing gemaakt
2021-05-18 Poging tot com BT - µC
2021-05-18 Voorbereiding verdediging
    poging tot meerdere effecten (code in apart bestand)
    Powerpoint gemaakt
    Verslag zo goed als af
2021-05-21 zo goed als laatste aanpassingen aan code/verslag
    propere code
    verslag bijna af
2021-05-21 Clear van bestanden + klaarmaken om up te loaden
    Onnodige bestanden verwijderd
    Verslag zo goed als af
2021-05-21 Verslag AF
2021-05-21 Verslag naar pdf gekopiëerd
2021-05-23 oefenen
